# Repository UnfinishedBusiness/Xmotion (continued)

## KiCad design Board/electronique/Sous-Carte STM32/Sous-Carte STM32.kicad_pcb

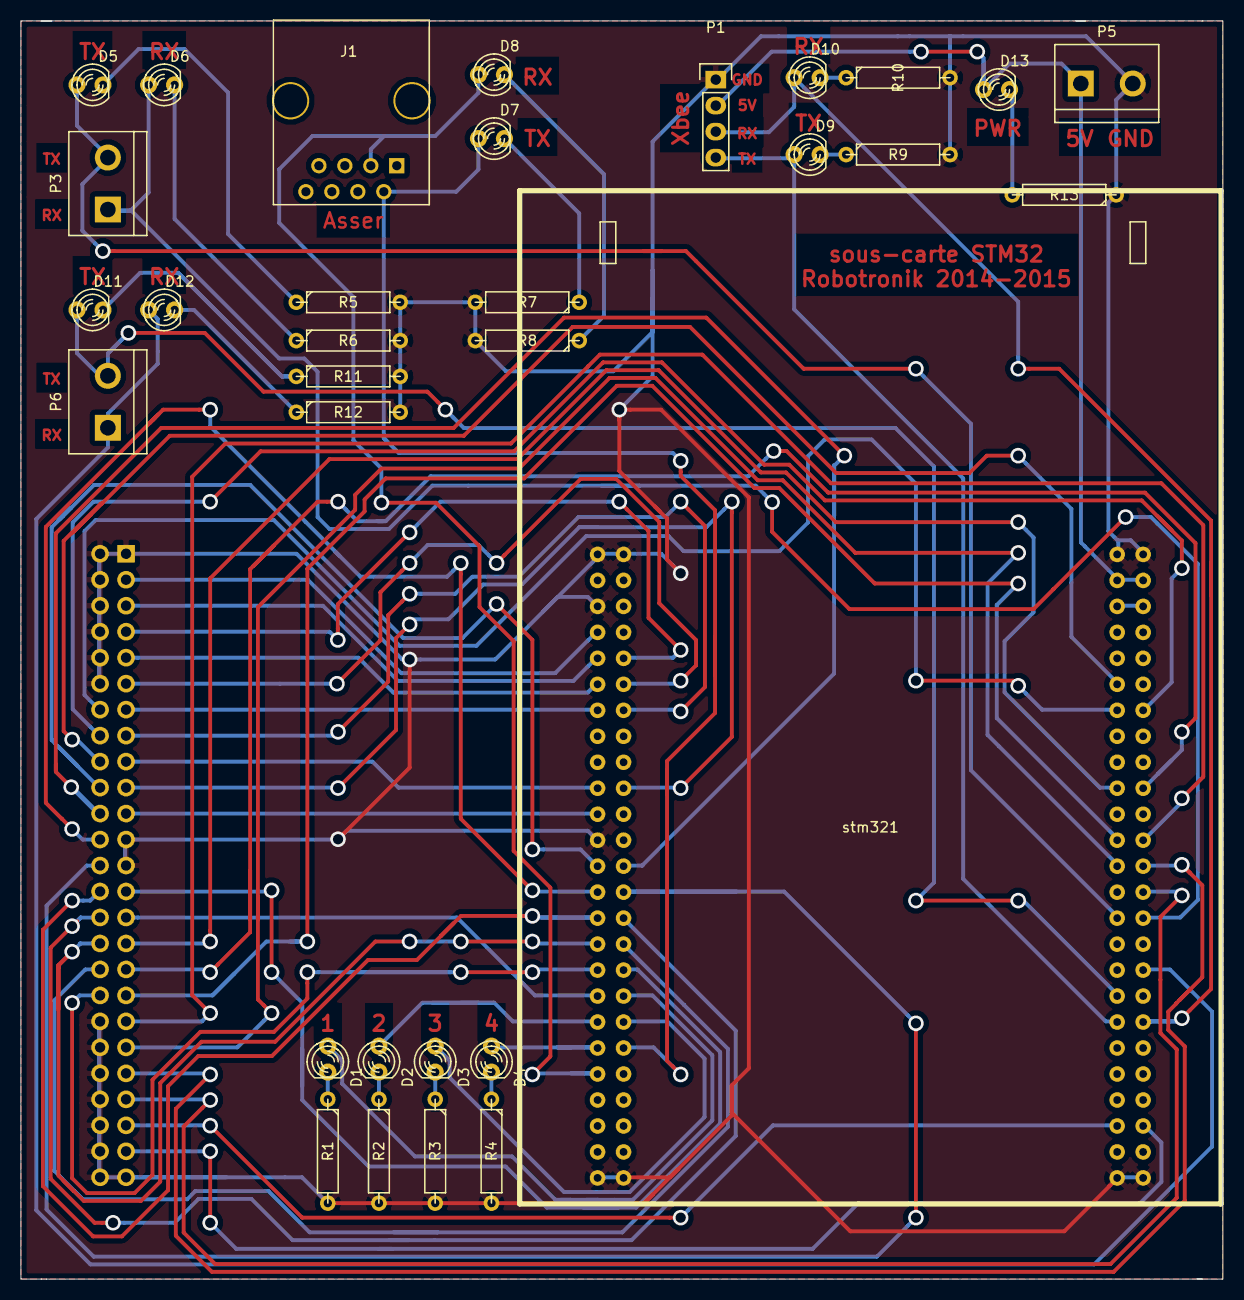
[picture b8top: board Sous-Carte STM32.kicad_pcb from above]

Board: 2 copper layers, 117.5 x 123.0 mm, 33 parts (1 on the bottom side), 61 nets.

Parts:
D1, D2, D3, D4, D5, D6, D7, D8, D9, D10, D11, D12, D13: LED; LED-3MM
J1: RJ45; RJ45_8
P1: CONN_01X04; Pin_Header_Straight_1x04
P3, P5, P6: CONN_01X02; bornier2
P7: CONN_02X25; Pin_Header_Straight_2x25
R1, R2, R3, R4, R5, R6, R7, R8, R9, R10, R11, R12, R13: R; R4
stm321: STM32F407-Discovery; STM32F407

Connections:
+3V3: stm321.55, stm321.56
+5V: D13.1, P1.2, P5.1, stm321.53, stm321.54
A0: P7.11, stm321.12
A1: P7.9, stm321.11
A2: P7.15, stm321.14
A3: P7.13, stm321.13
B1: P7.21, stm321.21
B3: P7.43, stm321.78
B4: P7.39, stm321.75
B5: P7.41, stm321.76
B6: P7.35, stm321.73
B7: P7.37, stm321.74
B8: P7.31, stm321.69
B9: P7.33, stm321.70
B10: P7.27, stm321.34
B11: P7.29, stm321.35
B12: D1.1, stm321.36
B13: D2.1, stm321.37
B14: D3.1, stm321.38
B15: D4.1, stm321.39
C1: P7.3, stm321.7
C2: P7.7, stm321.10
C3: P7.5, stm321.9
C4: P7.19, stm321.20
C5: P7.17, stm321.19
C8: P7.45, stm321.95
C9: P7.47, stm321.96
E4: P7.14, stm321.63
E5: P7.16, stm321.64
E6: P7.18, stm321.61
E7: P7.20, stm321.25
E8: P7.22, stm321.26
E9: P7.24, stm321.27
E10: P7.26, stm321.28
E11: P7.28, stm321.29
E12: P7.30, stm321.30
E13: P7.32, stm321.31
E14: P7.34, stm321.32
E15: P7.36, stm321.33
GND: P1.1, P5.2, P7.1, P7.2, P7.4, P7.6, P7.8, P7.10, P7.12, P7.23, P7.25, P7.38, P7.40, P7.42, P7.44, P7.46, P7.48, P7.49, P7.50, R1.2, R2.2, R3.2, R4.2, R5.2, R6.2, R7.2, R8.2, R9.2, R10.2, R11.2, R12.2, R13.1, stm321.1, stm321.2, stm321.5, stm321.23, stm321.49, stm321.50, stm321.51, stm321.52, stm321.99, stm321.100
unnamed: D1.2, R1.1
unnamed: D2.2, R2.1
unnamed: D3.2, R3.1
unnamed: D4.2, R4.1
unnamed: D5.2, R5.1
unnamed: D6.2, R6.1
unnamed: D7.2, R7.1
unnamed: D8.2, R8.1
unnamed: D9.2, R9.1
unnamed: D10.2, R10.1
unnamed: D11.2, R11.1
unnamed: D12.2, R12.1
unnamed: D13.2, R13.2
UART2_RX: D6.1, P3.1, stm321.80
UART2_TX: D5.1, P3.2, stm321.79
UART3_RX: D8.1, J1.3, stm321.41
UART3_TX: D7.1, J1.2, stm321.40
UART4_RX: D10.1, P1.3, stm321.88
UART4_TX: D9.1, P1.4, stm321.87
UART5_RX: D12.1, P6.1, stm321.84
UART5_TX: D11.1, P6.2, stm321.85
